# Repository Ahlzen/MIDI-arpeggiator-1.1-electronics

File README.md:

# MIDI-arpeggiator-1.1-electronics
Schematics and PCB design for MIDI Arpeggiator v1.1

For KiCad 7

Firmware at
https://github.com/Ahlzen/MIDI-arpeggiator-1.1-firmware

Case and panel at
https://github.com/Ahlzen/MIDI-arpeggiator-1.1-case

### 3rd Party Libraries used

Raspberry Pi Pico symbols, footprints and 3D models from
https://github.com/ncarandini/KiCad-RP-Pico
(CC-BY-SA 4.0)

Female DIN (MIDI) connector symbol and footprint from
https://github.com/nebs/eurocad

## Images and Resources

[PDF Schematic](Images/ArpeggiatorV1.1.pdf)

## TODO

* Pull in KiCAD-RP-Pico and Eurocad libraries as submodules. [Done]
* Ensure all components values on schematic + PCB silkscreen [Done]
* Include proper BOM and build notes
* Add photos of assembled PCB

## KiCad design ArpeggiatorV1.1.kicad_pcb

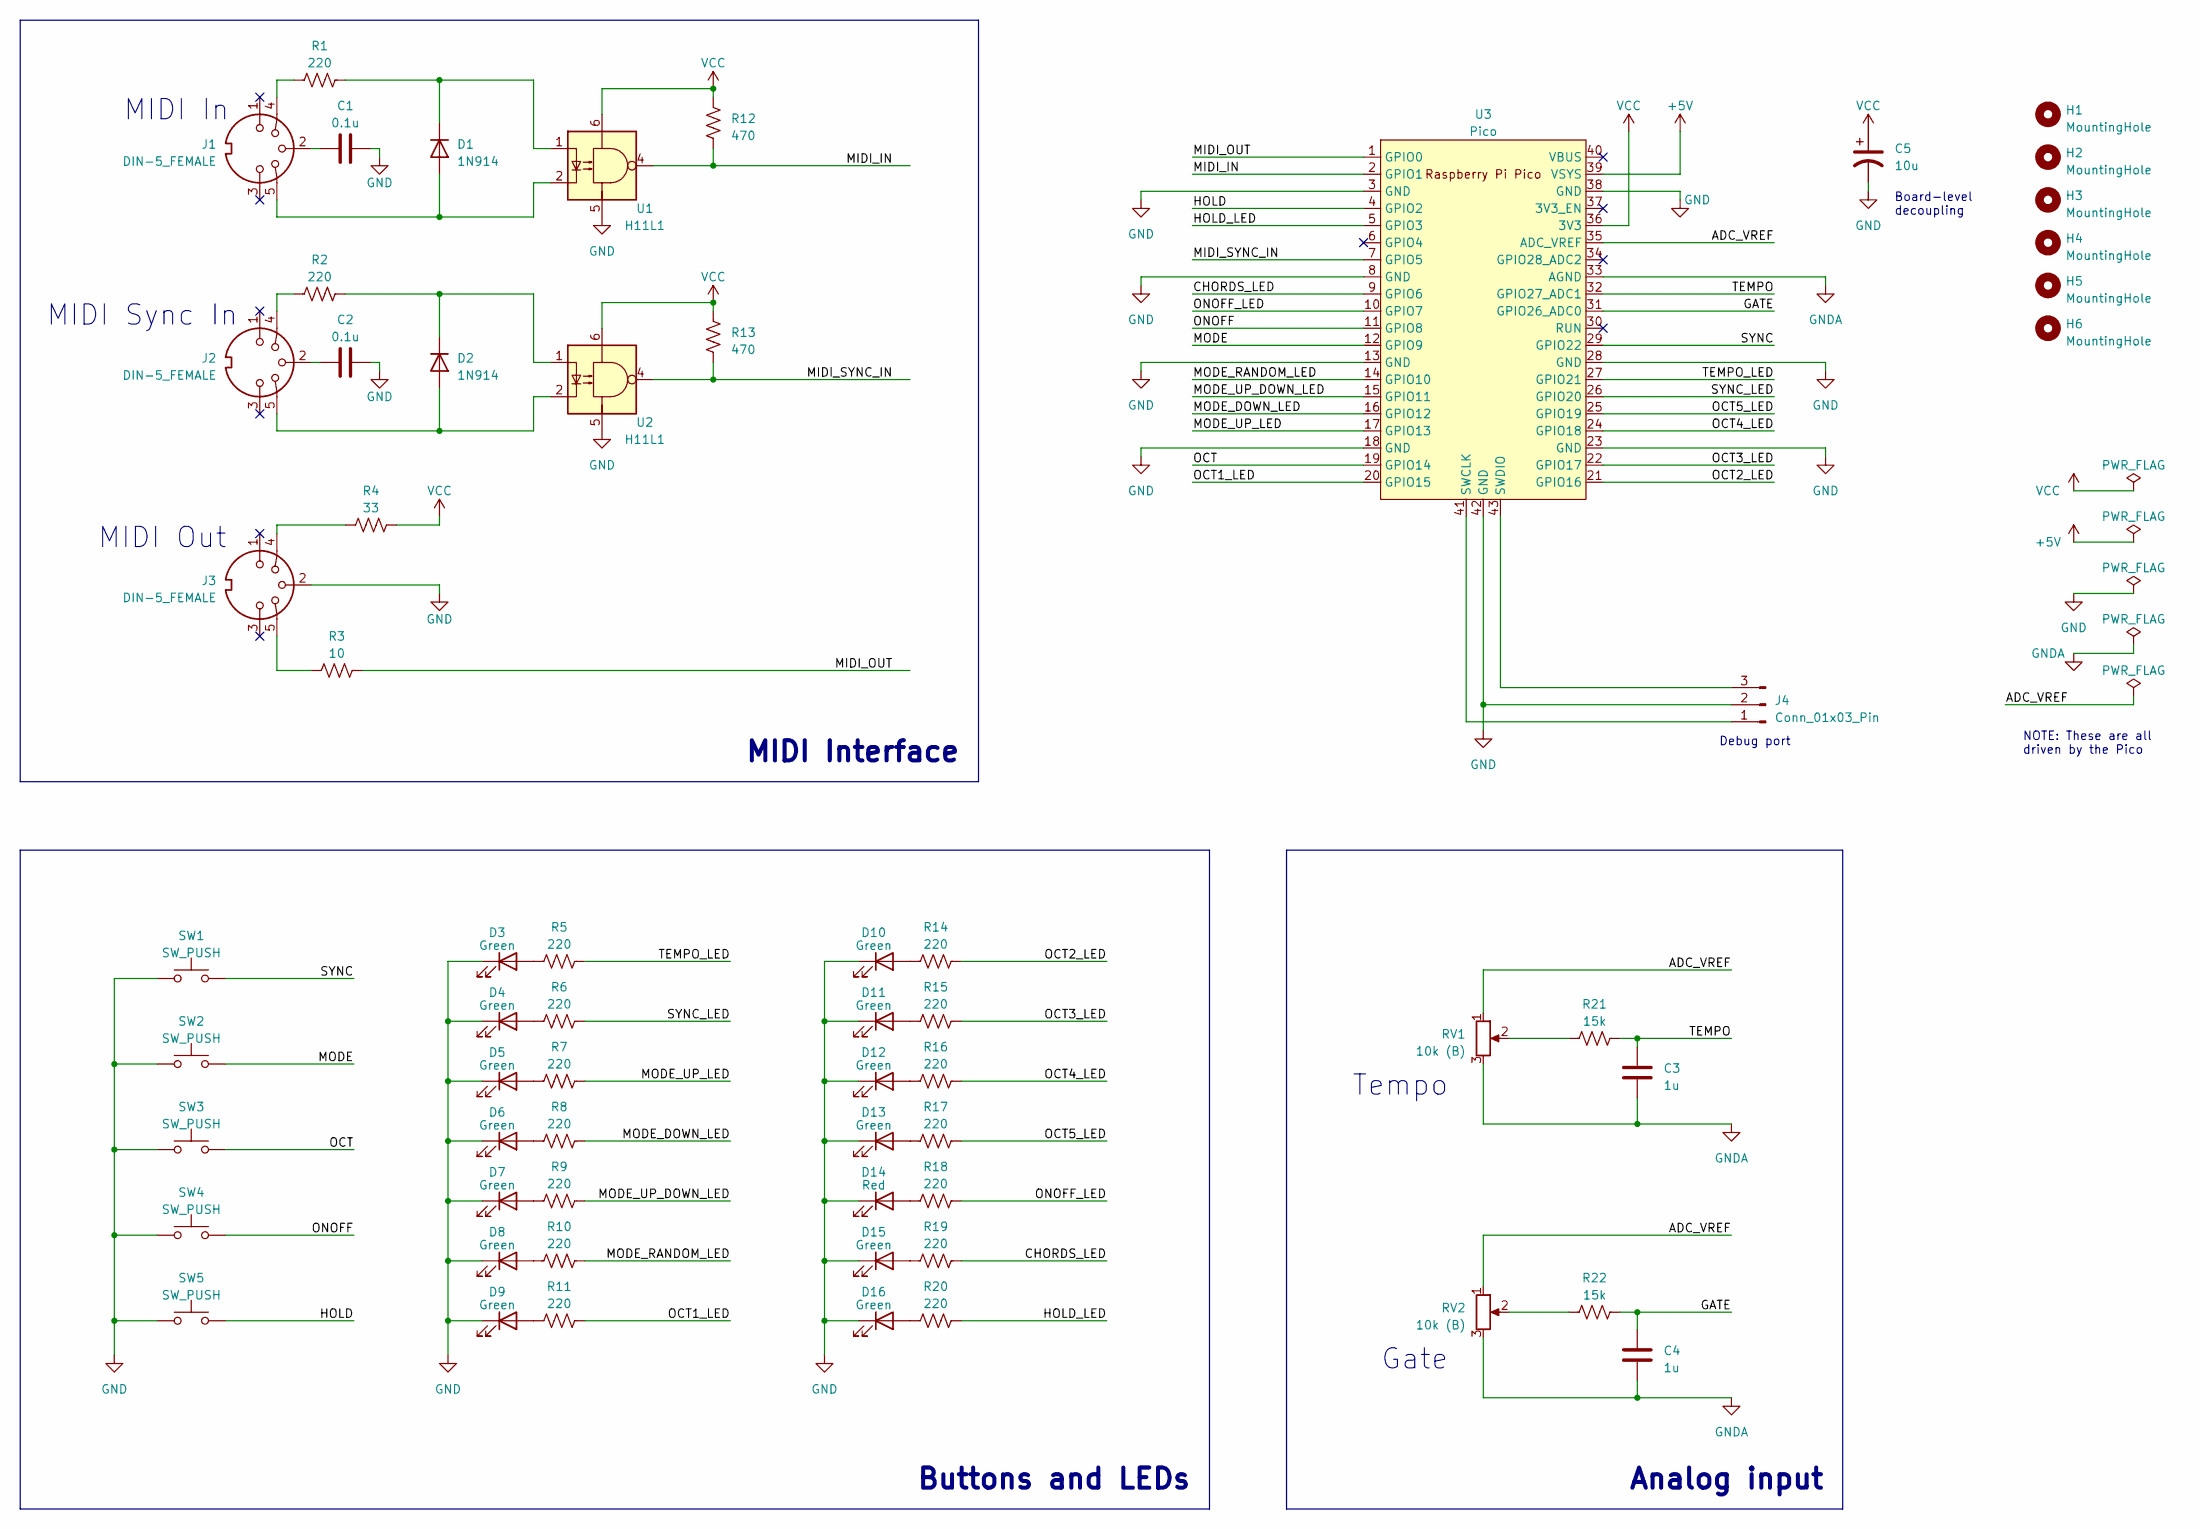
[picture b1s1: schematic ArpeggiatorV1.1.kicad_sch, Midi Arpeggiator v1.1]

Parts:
C1, C2: 0.1u; C_Disc_D3.0mm_W1.6mm_P2.50mm
C3, C4: 1u; C_Disc_D3.0mm_W1.6mm_P2.50mm
C5: 10u; CP_Radial_D5.0mm_P2.50mm
D1, D2: 1N914; D_A-405_P7.62mm_Horizontal
D3, D4, D5, D6, D7, D8, D9, D10, D11, D12, D13, D15, D16: Green; LED_D3.0mm
D14: Red; LED_D3.0mm
H1, H2, H3, H4, H5, H6: MountingHole; MountingHole_4mm
J1, J2, J3: DIN-5_FEMALE; MIDI_DIN5
J4: Conn_01x03_Pin; PinHeader_1x03_P2.54mm_Horizontal
R1, R2, R5, R6, R7, R8, R9, R10, R11, R14, R15, R16, R17, R18, R19, R20: 220; R_Axial_DIN0207_L6.3mm_D2.5mm_P10.16mm_Horizontal
R3: 10; R_Axial_DIN0207_L6.3mm_D2.5mm_P10.16mm_Horizontal
R4: 33; R_Axial_DIN0207_L6.3mm_D2.5mm_P10.16mm_Horizontal
R12, R13: 470; R_Axial_DIN0207_L6.3mm_D2.5mm_P10.16mm_Horizontal
R21, R22: 15k; R_Axial_DIN0207_L6.3mm_D2.5mm_P10.16mm_Horizontal
RV1, RV2: 10k (B); PinHeader_1x03_P2.54mm_Vertical
SW1, SW2, SW3, SW4, SW5: SW_PUSH; SW_PUSH_6mm
U1, U2: H11L1; DIP-6_W7.62mm_LongPads
U3: Pico; RPi_Pico_SMD_TH

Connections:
+5V: U3.39 (VSYS)
/ADC_VREF: RV1.1, RV2.1, U3.35 (ADC_VREF)
/CHORDS_LED: R19.2, U3.9 (GPIO6)
/GATE: C4.1, R22.2, U3.31 (GPIO26_ADC0)
/HOLD: SW5.2, U3.4 (GPIO2)
/HOLD_LED: R20.2, U3.5 (GPIO3)
/MIDI_IN: R12.2, U1.4, U3.2 (GPIO1)
/MIDI_OUT: R3.2, U3.1 (GPIO0)
/MIDI_SYNC_IN: R13.2, U2.4, U3.7 (GPIO5)
/MODE: SW2.2, U3.12 (GPIO9)
/MODE_DOWN_LED: R8.2, U3.16 (GPIO12)
/MODE_RANDOM_LED: R10.2, U3.14 (GPIO10)
/MODE_UP_DOWN_LED: R9.2, U3.15 (GPIO11)
/MODE_UP_LED: R7.2, U3.17 (GPIO13)
/OCT: SW3.2, U3.19 (GPIO14)
/OCT1_LED: R11.2, U3.20 (GPIO15)
/OCT2_LED: R14.2, U3.21 (GPIO16)
/OCT3_LED: R15.2, U3.22 (GPIO17)
/OCT4_LED: R16.2, U3.24 (GPIO18)
/OCT5_LED: R17.2, U3.25 (GPIO19)
/ONOFF: SW4.2, U3.11 (GPIO8)
/ONOFF_LED: R18.2, U3.10 (GPIO7)
/SYNC: SW1.2, U3.29 (GPIO22)
/SYNC_LED: R6.2, U3.26 (GPIO20)
/TEMPO: C3.1, R21.2, U3.32 (GPIO27_ADC1)
/TEMPO_LED: R5.2, U3.27 (GPIO21)
GND: C1.2, C2.2, C5.2, D3.1 (K), D4.1 (K), D5.1 (K), D6.1 (K), D7.1 (K), D8.1 (K), D9.1 (K), D10.1 (K), D11.1 (K), D12.1 (K), D13.1 (K), D14.1 (K), D15.1 (K), D16.1 (K), J3.2, J4.2, SW1.1, SW2.1, SW3.1, SW4.1, SW5.1, U1.5, U2.5, U3.3 (GND), U3.8 (GND), U3.13 (GND), U3.18 (GND), U3.23 (GND), U3.28 (GND), U3.38 (GND), U3.42 (GND)
GNDA: C3.2, C4.2, RV1.3, RV2.3, U3.33 (AGND)
unnamed: C1.1, J1.2
unnamed: C2.1, J2.2
unnamed: D1.2 (A), J1.5, U1.2
unnamed: D1.1 (K), R1.2, U1.1
unnamed: D2.2 (A), J2.5, U2.2
unnamed: D2.1 (K), R2.2, U2.1
unnamed: D3.2 (A), R5.1
unnamed: D4.2 (A), R6.1
unnamed: D5.2 (A), R7.1
unnamed: D6.2 (A), R8.1
unnamed: D7.2 (A), R9.1
unnamed: D8.2 (A), R10.1
unnamed: D9.2 (A), R11.1
unnamed: D10.2 (A), R14.1
unnamed: D11.2 (A), R15.1
unnamed: D12.2 (A), R16.1
unnamed: D13.2 (A), R17.1
unnamed: D14.2 (A), R18.1
unnamed: D15.2 (A), R19.1
unnamed: D16.2 (A), R20.1
unnamed: J1.4, R1.1
unnamed: J2.4, R2.1
unnamed: J3.4, R4.1
unnamed: J3.5, R3.1
unnamed: J4.1, U3.41 (SWCLK)
unnamed: J4.3, U3.43 (SWDIO)
unnamed: R21.1, RV1.2
unnamed: R22.1, RV2.2
VCC: C5.1, R4.2, R12.1, R13.1, U1.6, U2.6, U3.36 (3V3)

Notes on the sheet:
Gate
Board-level decoupling
Buttons and LEDs
MIDI In
MIDI Out
NOTE: These are all driven by the Pico
Tempo
Analog input
MIDI Interface
MIDI Sync In
Debug port

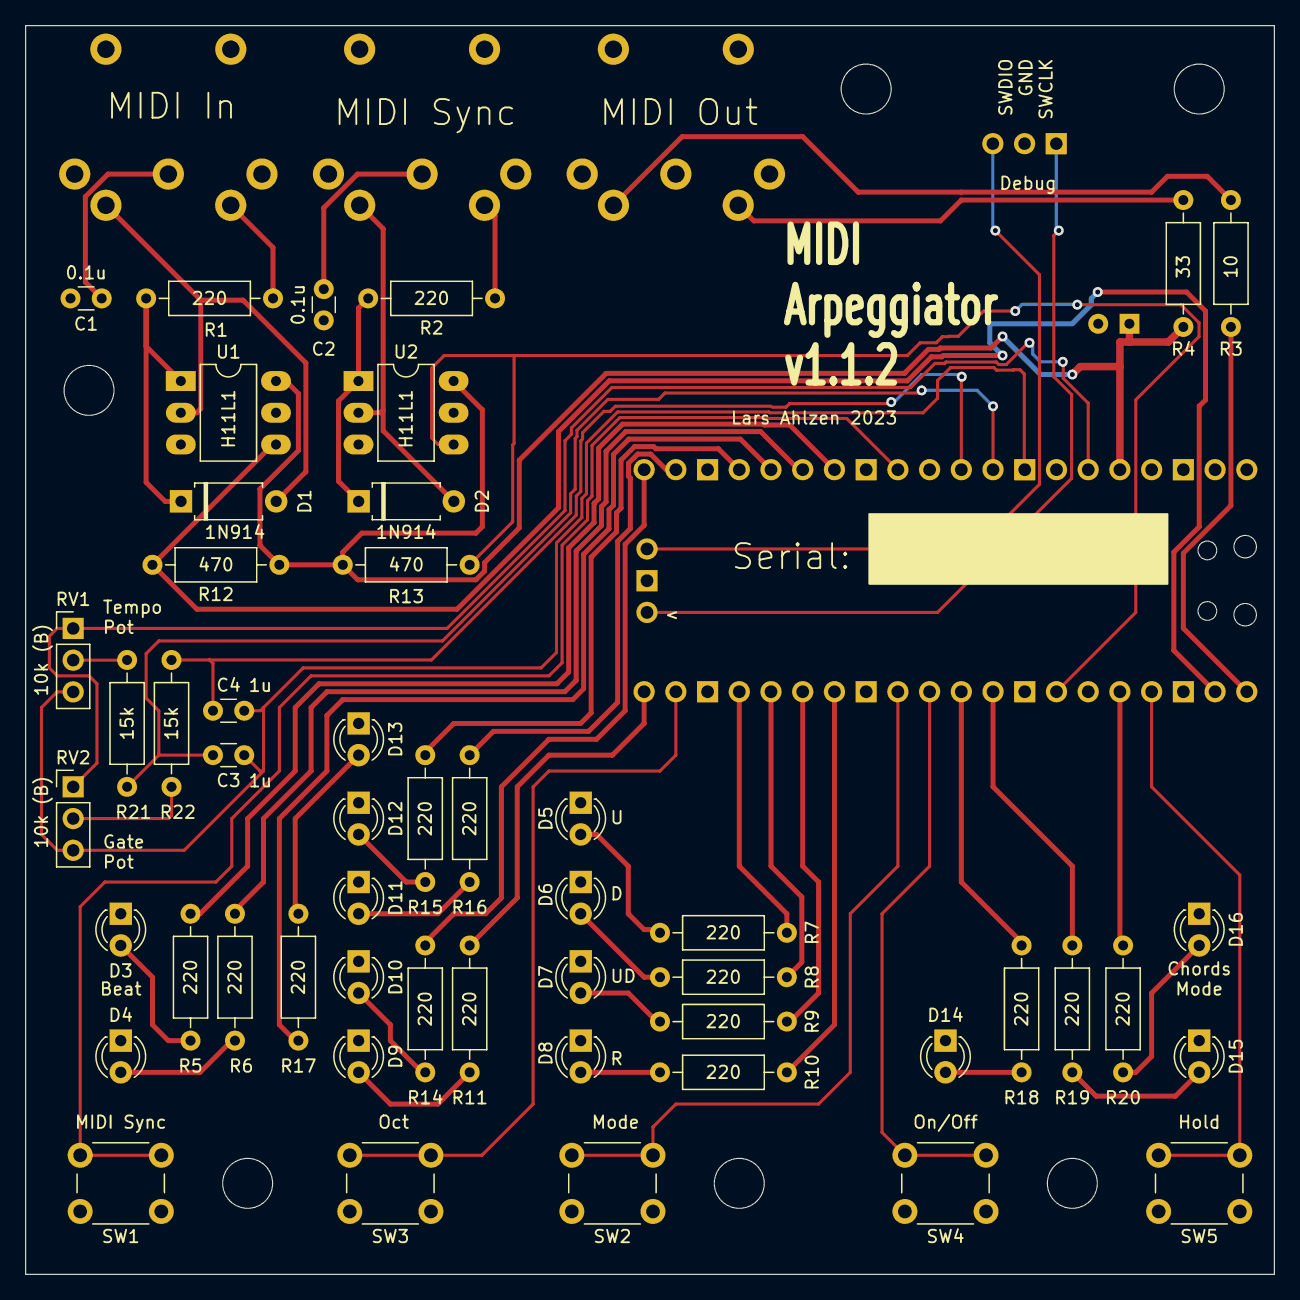
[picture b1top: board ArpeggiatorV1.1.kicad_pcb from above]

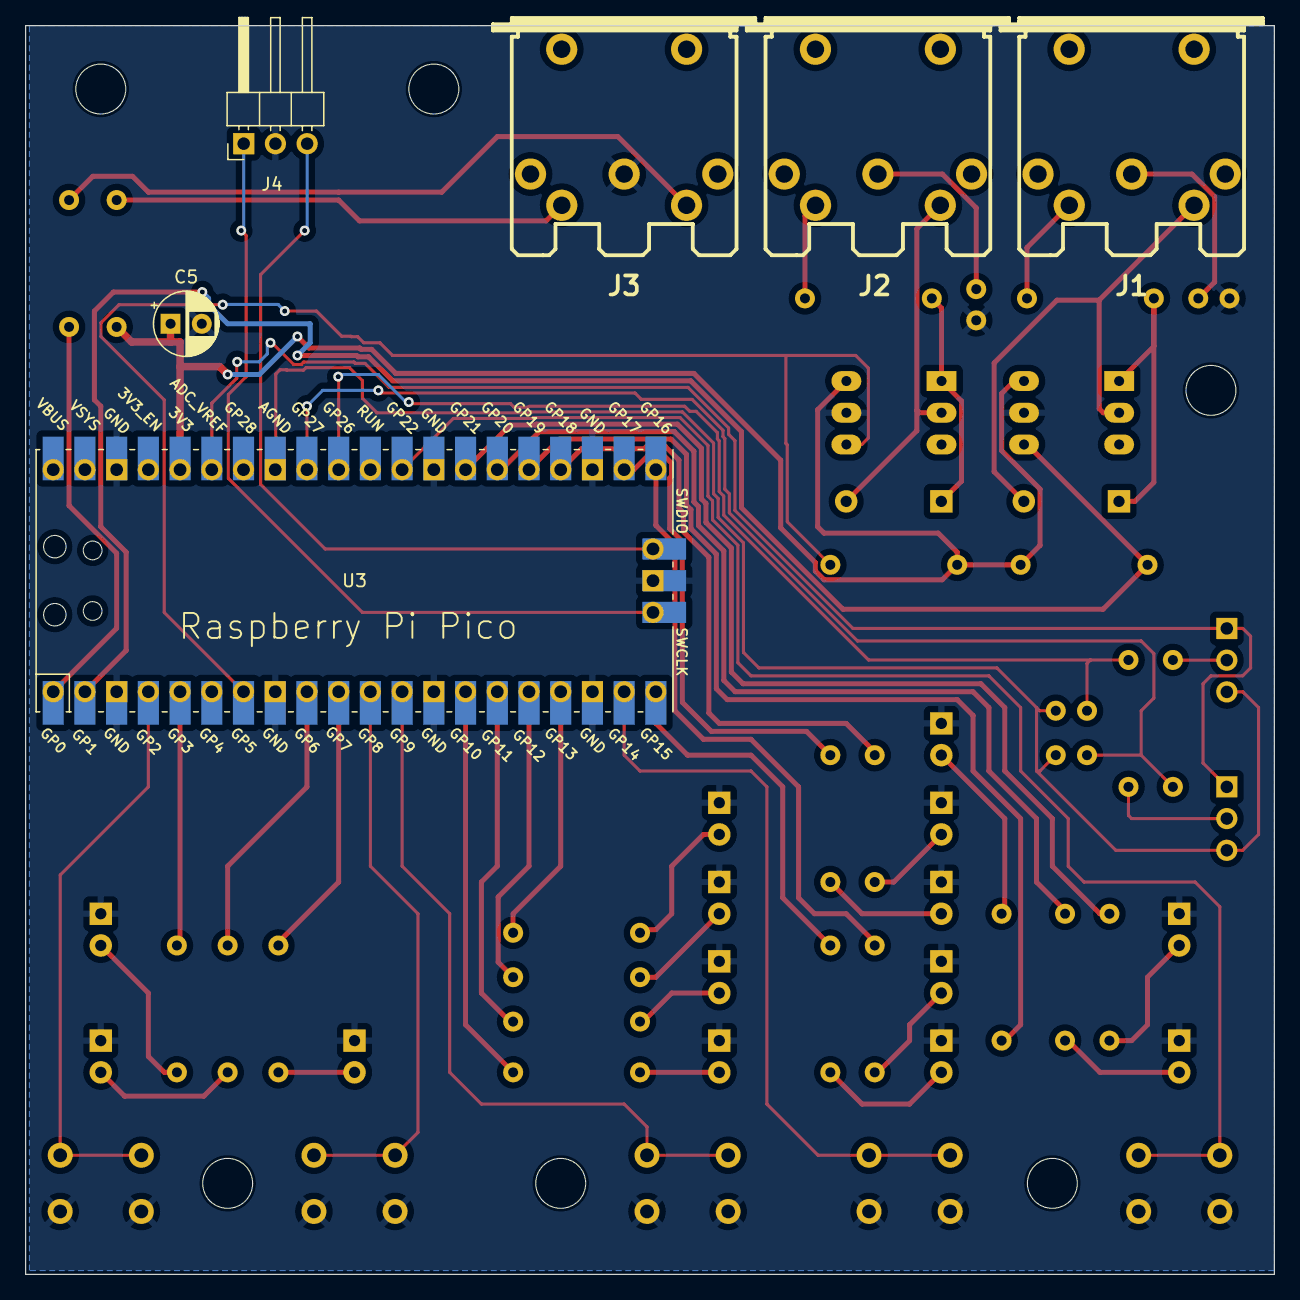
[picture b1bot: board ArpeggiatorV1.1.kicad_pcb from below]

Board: 2 copper layers, 100.0 x 100.0 mm, 63 parts (6 on the bottom side), 56 nets.

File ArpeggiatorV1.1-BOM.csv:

"Reference","Value","Footprint","Qty"
"C1, C2","0.1u","Capacitor_THT:C_Disc_D3.0mm_W1.6mm_P2.50mm","2"
"C3, C4","1u","Capacitor_THT:C_Disc_D3.0mm_W1.6mm_P2.50mm","2"
"C5","10u","Capacitor_THT:CP_Radial_D5.0mm_P2.50mm","1"
"D1, D2","1N914","Diode_THT:D_A-405_P7.62mm_Horizontal","2"
"D3-D13, D15, D16","Green","LED_THT:LED_D3.0mm","13"
"D14","Red","LED_THT:LED_D3.0mm","1"
"H1-H6","MountingHole","MountingHole:MountingHole_4mm","6"
"J1-J3","DIN-5_FEMALE","Eurocad:MIDI_DIN5","3"
"J4","Conn_01x03_Pin","Connector_PinHeader_2.54mm:PinHeader_1x03_P2.54mm_Horizontal","1"
"R1, R2, R5-R11, R14-R20","220","Resistor_THT:R_Axial_DIN0207_L6.3mm_D2.5mm_P10.16mm_Horizontal","16"
"R3","10","Resistor_THT:R_Axial_DIN0207_L6.3mm_D2.5mm_P10.16mm_Horizontal","1"
"R4","33","Resistor_THT:R_Axial_DIN0207_L6.3mm_D2.5mm_P10.16mm_Horizontal","1"
"R12, R13","470","Resistor_THT:R_Axial_DIN0207_L6.3mm_D2.5mm_P10.16mm_Horizontal","2"
"R21, R22","15k","Resistor_THT:R_Axial_DIN0207_L6.3mm_D2.5mm_P10.16mm_Horizontal","2"
"RV1, RV2","10k (B)","Connector_PinHeader_2.54mm:PinHeader_1x03_P2.54mm_Vertical","2"
"SW1-SW5","SW_PUSH","Button_Switch_THT:SW_PUSH_6mm","5"
"U1, U2","H11L1","Package_DIP:DIP-6_W7.62mm_LongPads","2"
"U3","Pico","MCU_RaspberryPi_and_Boards:RPi_Pico_SMD_TH","1"

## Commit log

2023-04-07 Initial schematic.
2023-04-07 Added README.md
2023-04-07 Cleaned up schematic
2023-04-07 Added "Eurocad" KiCAD symbol/footprint library
2023-04-07 Updated component footprints. Set initial PCB design rules for common prototyping houses like PCBWay and OSHPark.
2023-04-14 Adjusted pin assigments for a cleaner layout. Partially laid out and routed board.
2023-04-14 Mostly finished PCB layout.
2023-04-14 Finished routing missing signals.
2023-04-14 Cleaned up PCB and fixed some DRC warnings.
2023-04-14 Fixed minor PCB issues.
2023-04-14 More minor PCB adjustments.
2023-04-14 Added gerbers + drill files.
2023-04-14 Cleaned up labels on schematic.
2023-04-15 Added PCB and schematic images for readme.
2023-04-15 Added images to readme.
2023-04-15 Added notes about mechanical layout (locations of panel/case elements)
2023-04-15 Minor PCB corrections and cleanups.
2023-04-18 Fixed typos in Mechanical layout.txt
2023-04-29 Added TODO list in Readme.
2023-04-29 Added component values to PCB silkscreen.
2023-04-30 Added 3rd party kicad libraries as submodules.
2023-06-30 Added initial CHANGELOG.
2023-07-01 Updated schematic+PCB with new MIDI interface section.
2023-07-01 Updated gerbers, images and changelog.
2023-07-01 Included bill-of-materials.
2023-07-01 Added actual BOM file.
2023-07-01 Updated schematic thumbnail image.
2023-07-25 Fixed PCB routing error for TEMPO net. Cleaned up some PCB labels on silkscreen.
2023-09-11 Added photo of case.
